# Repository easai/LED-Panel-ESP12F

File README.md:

# LED Panel ESP‑12F

The HTML page is available in this GitHub repository:
[https://easai.github.io/LED-Panel-ESP12F/](https://easai.github.io/LED-Panel-ESP12F/)

A compact ESP‑12F–based controller board designed to drive an 8×8 LED panel with an onboard buzzer, stable power regulation, and reliable programming support. This project was completed with the generous support of my sponsor, whose fabrication assistance transformed a fragile prototype into a robust, reproducible hardware platform.

## Sponsor Acknowledgment

This project reached completion thanks to the support of <a href="https://www.pcbway.com/" target="_blank" title="PCBWay">PCBWay</a>, who provided fabrication assistance that transformed the prototype into a clean, reliable PCB. Before fabrication, the prototype relied on a dense web of jumper wires, loose connections, and constant troubleshooting. With my sponsor’s help, the design moved from that unstable setup to a clean, professionally manufactured PCB that is easy to assemble, reliable to operate, and ready for long‑term use.

Their contribution directly improved electrical stability, mechanical reliability, assembly clarity, and long‑term maintainability. The contrast between the prototype and the final board demonstrates the real value of proper PCB fabrication.

## Breadboard Prototype → PCB Assembly

### Before: Breadboard-based Prototype  
The initial version worked, but the wiring was messy, fragile, and difficult to debug. It served its purpose for early validation, but it was not suitable for repeated use or documentation.  

<div class="flex">

</div>

### After: Assembled PCB  
The final PCB was fabricated by PCBWay, whose manufacturing quality made the design stable, durable, and easy to assemble. The board programs correctly, executes firmware without issues, and drives the LED panel and buzzer exactly as intended.  

This comparison highlights the impact of fabrication support and the improvement in overall quality.

## Programming the ESP‑12F Using an FTDI Adapter

The ESP‑12F can be programmed directly through a USB‑to‑serial adapter such as an FTDI module. The board includes a dedicated programming header, making the upload process reliable and repeatable.

To enter programming mode, the ESP‑12F requires specific boot pin states during reset. The PCB handles these automatically through pull‑ups and pull‑downs, so only four connections are needed from the FTDI adapter:

Before uploading, connect the FTDI module to the programming header as shown below.

• FTDI TX → Programming header TX  
• FTDI RX → Programming header RX  
• FTDI GND → Programming header GND  

Once connected:

1. Press and hold the BOOT button.  
2. Tap RESET.  
3. Release BOOT.  
4. Upload the firmware from your IDE (Arduino IDE or PlatformIO).  

The board will automatically reboot into normal operation after programming. This workflow ensures consistent flashing without the wiring errors common in breadboard prototypes.

## Configuration

Copy `config.h.sample` to `config.h` and fill in your network details.

`config.h` contains:
- `SECRET_SSID` for the WiFi network name
- `SECRET_PASS` for the WiFi password
- `SITE_URL` for the target endpoint

`config.h` is not tracked in the repository. Users must create it before building the firmware.

## Hardware Overview

The board integrates an ESP‑12F module, 5 V to 3.3 V regulation, LED panel connector, buzzer with mute control, programming header, clear silkscreen labeling, and a stable power and ground layout. All hardware files are included for reproducibility.

### Schematic

### Board Layout

## Software

This firmware provides a stable demonstration of the ESP12F board and verifies that the PCB, power routing, and peripherals operate correctly. The program in main.cpp is structured around predictable, nonblocking timing and focuses on hardware validation rather than feature development.

### Boot and Initialization
The program configures all required GPIO pins for the LED panel, buzzer, mute switch, and status LED. It initializes the MAX7219 driver, clears the display, and starts serial output for debugging. This confirms that the ESP12F boots correctly after flashing.

### LED Panel Operation
The MAX7219 driver is initialized, and the panel is updated at fixed intervals using timestamp checks instead of delay. A simple pattern or text is shown to verify panel wiring, power stability, and refresh behavior. The update routine is nonblocking, so the device remains responsive.

### Buzzer and Mute Button
The buzzer is controlled through a digital output pin. The mute button is read continuously and suppresses buzzer output when pressed. This logic runs without blocking the main loop and confirms the correct routing of the switch and buzzer.

### WiFi Startup
WiFi initialization is included to confirm that the module boots into the correct mode and that RF components are functional. Connection status is printed to serial. No network features are implemented in this version.

### Main Loop Structure
The loop uses millisecond timestamps to schedule tasks. LED updates, button reads, and buzzer logic run at defined intervals. No blocking delays are used. This structure ensures reproducible behavior and provides a foundation for future animation or network features.

### Purpose of This Version
This firmware is intended for hardware validation. It confirms correct boot behavior, verifies the LED panel, buzzer, and button, and establishes a stable base for future development.

## Repository Structure

- hardware/kicad/ contains the KiCad schematic and PCB files  
- hardware/fabrication/ contains Gerbers, BOM
- hardware/images/ contains schematic, PCB front/back, prototype wiring, and assembled PCB images  
- README.md is this document

## Bill of Materials

A complete BOM is available in <a href="https://github.com/easai/LED-Panel-ESP12F/blob/main/hardware/fabrication/LED-Panel-ESP12F-bom.csv" target="_blank" title="LED-Panel-ESP12F BOM">hardware/fabrication/LED-Panel-ESP12F-bom.csv</a>.

## Credits

PCB fabrication provided by PCBWay.

The LED matrix case used in this project is my own remix, published at <a href="https://www.printables.com/" title="Printables.com" target="_blank">Printables</a>:  
<a href="https://www.printables.com/model/1476658-4-in-1-led-dot-matrix-mount" title="4-in-1 LED Dot Matrix Mount" target="_blank">4-in-1 LED Dot Matrix Mount</a>

## License

MIT License

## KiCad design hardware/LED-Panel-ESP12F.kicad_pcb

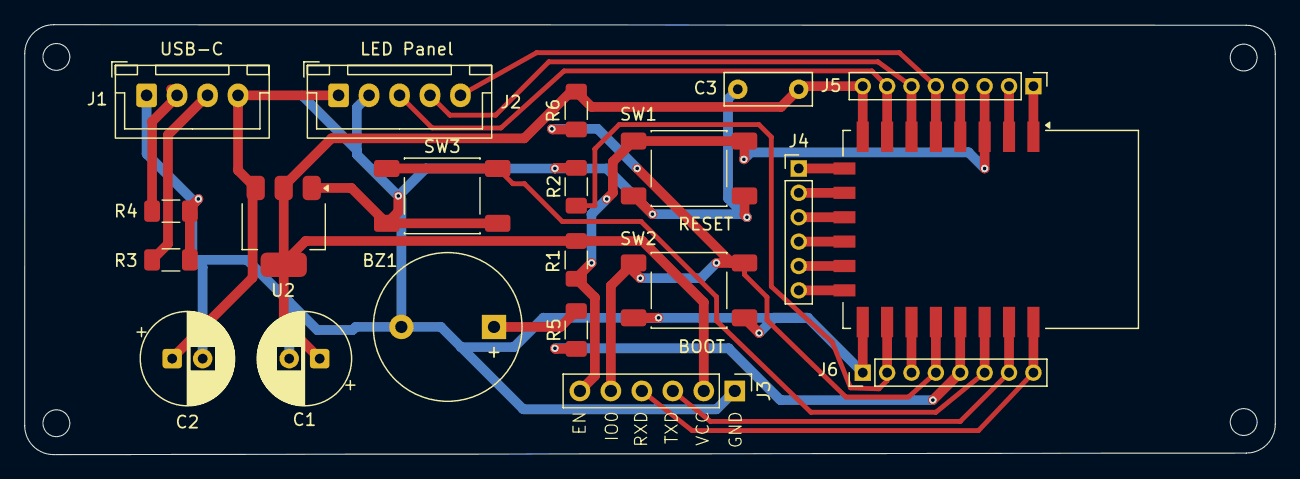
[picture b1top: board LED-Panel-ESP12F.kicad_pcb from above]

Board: 2 copper layers, 102.6 x 35.3 mm, 21 parts (0 on the bottom side), 26 nets.

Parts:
BZ1: Buzzer; MagneticBuzzer_StarMicronics_TMB
C1, C2: 100uF; CP_Radial_D7.5mm_P2.50mm
C3: 0.1 uF; C_Disc_D7.0mm_W2.5mm_P5.00mm
J1: USB-C; JST_XH_B4B-XH-A_1x04_P2.50mm_Vertical
J2: LED Panel; JST_XH_B5B-XH-A_1x05_P2.50mm_Vertical
J3: Programming Header; PinHeader_1x06_P2.54mm_Vertical
J4: Conn_01x06_Pin; PinHeader_1x06_P2.00mm_Vertical
J5, J6: Conn_01x08_Pin; PinHeader_1x08_P2.00mm_Vertical
R1, R2, R6: 10k; R_1206_3216Metric_Pad1.30x1.75mm_HandSolder
R3, R4: 5.1k; R_1206_3216Metric_Pad1.30x1.75mm_HandSolder
R5: 100; R_1206_3216Metric_Pad1.30x1.75mm_HandSolder
SW1: RESET; SW_Push_1P1T_NO_E-Switch_TL3301NxxxxxG
SW2: BOOT; SW_Push_1P1T_NO_E-Switch_TL3301NxxxxxG
SW3: MUTE; SW_Push_1P1T_NO_E-Switch_TL3301NxxxxxG
U1: ESP-12F; ESP-12E
U2: AMS1117-3.3; SOT-223-3_TabPin2

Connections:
GND: BZ1.2 (-), C1.2, C2.2, C3.2, J1.1, J2.2, J3.1, J6.1, R2.2, R3.2, R4.2, SW1.2, SW2.2, SW3.2, U1.15 (GND), U2.1 (GND)
unnamed: BZ1.1 (+), R5.2
unnamed: J1.2, R4.1
unnamed: J1.3, R3.1
unnamed: C2.1, J1.4, J2.1, U2.3 (VI)
unnamed: J2.3, J5.7, U1.7 (GPIO13)
unnamed: J2.4, J5.6, U1.6 (GPIO12)
unnamed: J2.5, J5.5, U1.5 (GPIO14)
unnamed: C1.1, C3.1, J3.2, J5.8, R1.1, R6.1, U1.8 (VCC), U2.2 (VO)
unnamed: J3.3, J6.7, U1.21 (GPIO3/RXD)
unnamed: J3.4, J6.8, U1.22 (GPIO1/TXD)
unnamed: J3.5, J6.4, R6.2, SW2.1, U1.18 (GPIO0)
unnamed: J3.6, J5.3, R1.2, SW1.1, U1.3 (EN)
unnamed: J4.1, U1.9 (CS0)
unnamed: J4.2, U1.10 (MISO)
unnamed: J4.3, U1.11 (GPIO9)
unnamed: J4.4, U1.12 (GPIO10)
unnamed: J4.5, U1.13 (MOSI)
unnamed: J4.6, U1.14 (SCLK)
unnamed: J5.1, U1.1 (~RST)
unnamed: J5.2, U1.2 (ADC)
unnamed: J5.4, U1.4 (GPIO16)
unnamed: J6.2, R2.1, U1.16 (GPIO15)
unnamed: J6.3, U1.17 (GPIO2)
unnamed: J6.5, R5.1, U1.19 (GPIO4)
unnamed: J6.6, SW3.1, U1.20 (GPIO5)

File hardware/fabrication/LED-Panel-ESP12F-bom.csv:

"Reference","Qty","Value","DNP","Exclude from BOM","Exclude from Board","Footprint","Datasheet"
"BZ1","1","Buzzer","","","","Buzzer_Beeper:MagneticBuzzer_StarMicronics_TMB","~"
"C1,C2","2","100uF","","","","Capacitor_THT:CP_Radial_D7.5mm_P2.50mm","~"
"C3","1","0.1 uF","","","","Capacitor_THT:C_Disc_D7.0mm_W2.5mm_P5.00mm","~"
"J1","1","USB-C","","","","Connector_JST:JST_XH_B4B-XH-A_1x04_P2.50mm_Vertical","~"
"J2","1","LED Panel","","","","Connector_JST:JST_XH_B5B-XH-A_1x05_P2.50mm_Vertical","~"
"J3","1","Programming Header","","","","Connector_PinHeader_2.54mm:PinHeader_1x06_P2.54mm_Vertical","~"
"J4","1","Conn_01x06_Pin","","","","Connector_PinHeader_2.00mm:PinHeader_1x06_P2.00mm_Vertical","~"
"J5,J6","2","Conn_01x08_Pin","","","","Connector_PinHeader_2.00mm:PinHeader_1x08_P2.00mm_Vertical","~"
"R1,R2,R6","3","10k ohm","","","","Resistor_SMD:R_1206_3216Metric_Pad1.30x1.75mm_HandSolder","~"
"R3,R4","2","5.1k ohm","","","","Resistor_SMD:R_1206_3216Metric_Pad1.30x1.75mm_HandSolder","~"
"R5","1","100 ohm","","","","Resistor_SMD:R_1206_3216Metric_Pad1.30x1.75mm_HandSolder","~"
"SW1","1","RESET","","","","Button_Switch_SMD:SW_Push_1P1T_NO_E-Switch_TL3301NxxxxxG","~"
"SW2","1","BOOT","","","","Button_Switch_SMD:SW_Push_1P1T_NO_E-Switch_TL3301NxxxxxG","~"
"SW3","1","MUTE","","","","Button_Switch_SMD:SW_Push_1P1T_NO_E-Switch_TL3301NxxxxxG","~"
"U1","1","ESP-12F","","","","RF_Module:ESP-12E","http://wiki.ai-thinker.com/_media/esp8266/esp8266_series_mod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"
"U2","1","AMS1117-3.3","","","","Package_TO_SOT_SMD:SOT-223-3_TabPin2","http://www.advanced-monolithic.com/pdf/ds1117.pdf"

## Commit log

2026-01-13 add pcb image
2026-01-26 Add hardware files
2026-01-26 Remove .vscode directory from repository
2026-01-26 Edit breadboard image
2026-01-26 Add schematic PNG
2026-01-26 Update README with schematic and board layout
    Added schematic and board layout images to README.
2026-01-26 Add assembled PCB image to README
    Added image of assembled PCB to the README.
2026-01-27 Update site monitor program.
2026-01-27 Add webpage.
2026-01-27 Fix HTML page link in README
    Updated the link to the HTML page in the README.
2026-01-28 Optimized main.cpp.
2026-01-28 Update index.html. Add unit test files.
2026-01-28 Remove old files.
2026-01-28 Update index.html.
2026-01-28 Add config.h.sample.
2026-01-28 Update README formatting for configuration section
2026-01-28 Update the credit section.
2026-02-02 Add wiring GIF
2026-02-02 Update README with FTDI adapter programming details
    Added wiring diagram and connection instructions for FTDI adapter.
2026-02-02 Update wiring GIF
2026-02-02 Move parts image to images directory
2026-02-02 Create demo GIF
2026-02-02 Enhance README with images of prototypes
    Added images to illustrate the breadboard prototype and final PCB.
2026-02-05 Add a poster version
2026-02-05 Enhance README with prototype image and details
    Added an image and description of the breadboard-based prototype.
2026-02-05 Update section title from 'Before and After' to 'From breadboard prototype to PCB'
2026-02-05 Change section title from 'From breadboard prototype to PCB' to 'Breadboard Prototype → PCB Assembly'
    Updated section title for clarity and consistency.
2026-02-05 Rename poster image file
2026-02-05 Replace prototype image with final PCB image
    Updated image in README to reflect final PCB assembly.
